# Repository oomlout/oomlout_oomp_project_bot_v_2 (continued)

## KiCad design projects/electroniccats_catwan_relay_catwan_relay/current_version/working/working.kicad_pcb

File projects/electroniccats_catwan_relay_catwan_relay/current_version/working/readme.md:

# catwan_relay
 
## summary 
* id: electroniccats_catwan_relay_catwan_relay
* user: electroniccats
* name: catwan_relay
* board: catwan_relay
* repo: https://github.com/ElectronicCats/CatWAN_Relay
* src_file_repo_kicad_pcb: Hw/CatWAN-Relay.kicad_pcb
* src_file_repo_kicad_pcb_link: https://github.com/ElectronicCats/CatWAN_Relay/tree/master/Hw/CatWAN-Relay.kicad_pcb
* src_file_repo_kicad_sch: Hw/CatWAN-Relay.kicad_sch
* src_file_repo_kicad_sch_link: https://github.com/ElectronicCats/CatWAN_Relay/tree/master/Hw/CatWAN-Relay.kicad_sch

* src_file_repo_sch: Hw/CatWAN-Relay.sch
* src_file_repo_sch_link: https://github.com/ElectronicCats/CatWAN_Relay/tree/master/Hw/CatWAN-Relay.sch
* full details link: https://github.com/oomlout/oomlout_oomp_project_bot_v_2/tree/main/projects/electroniccats_catwan_relay_catwan_relay/current_version/working

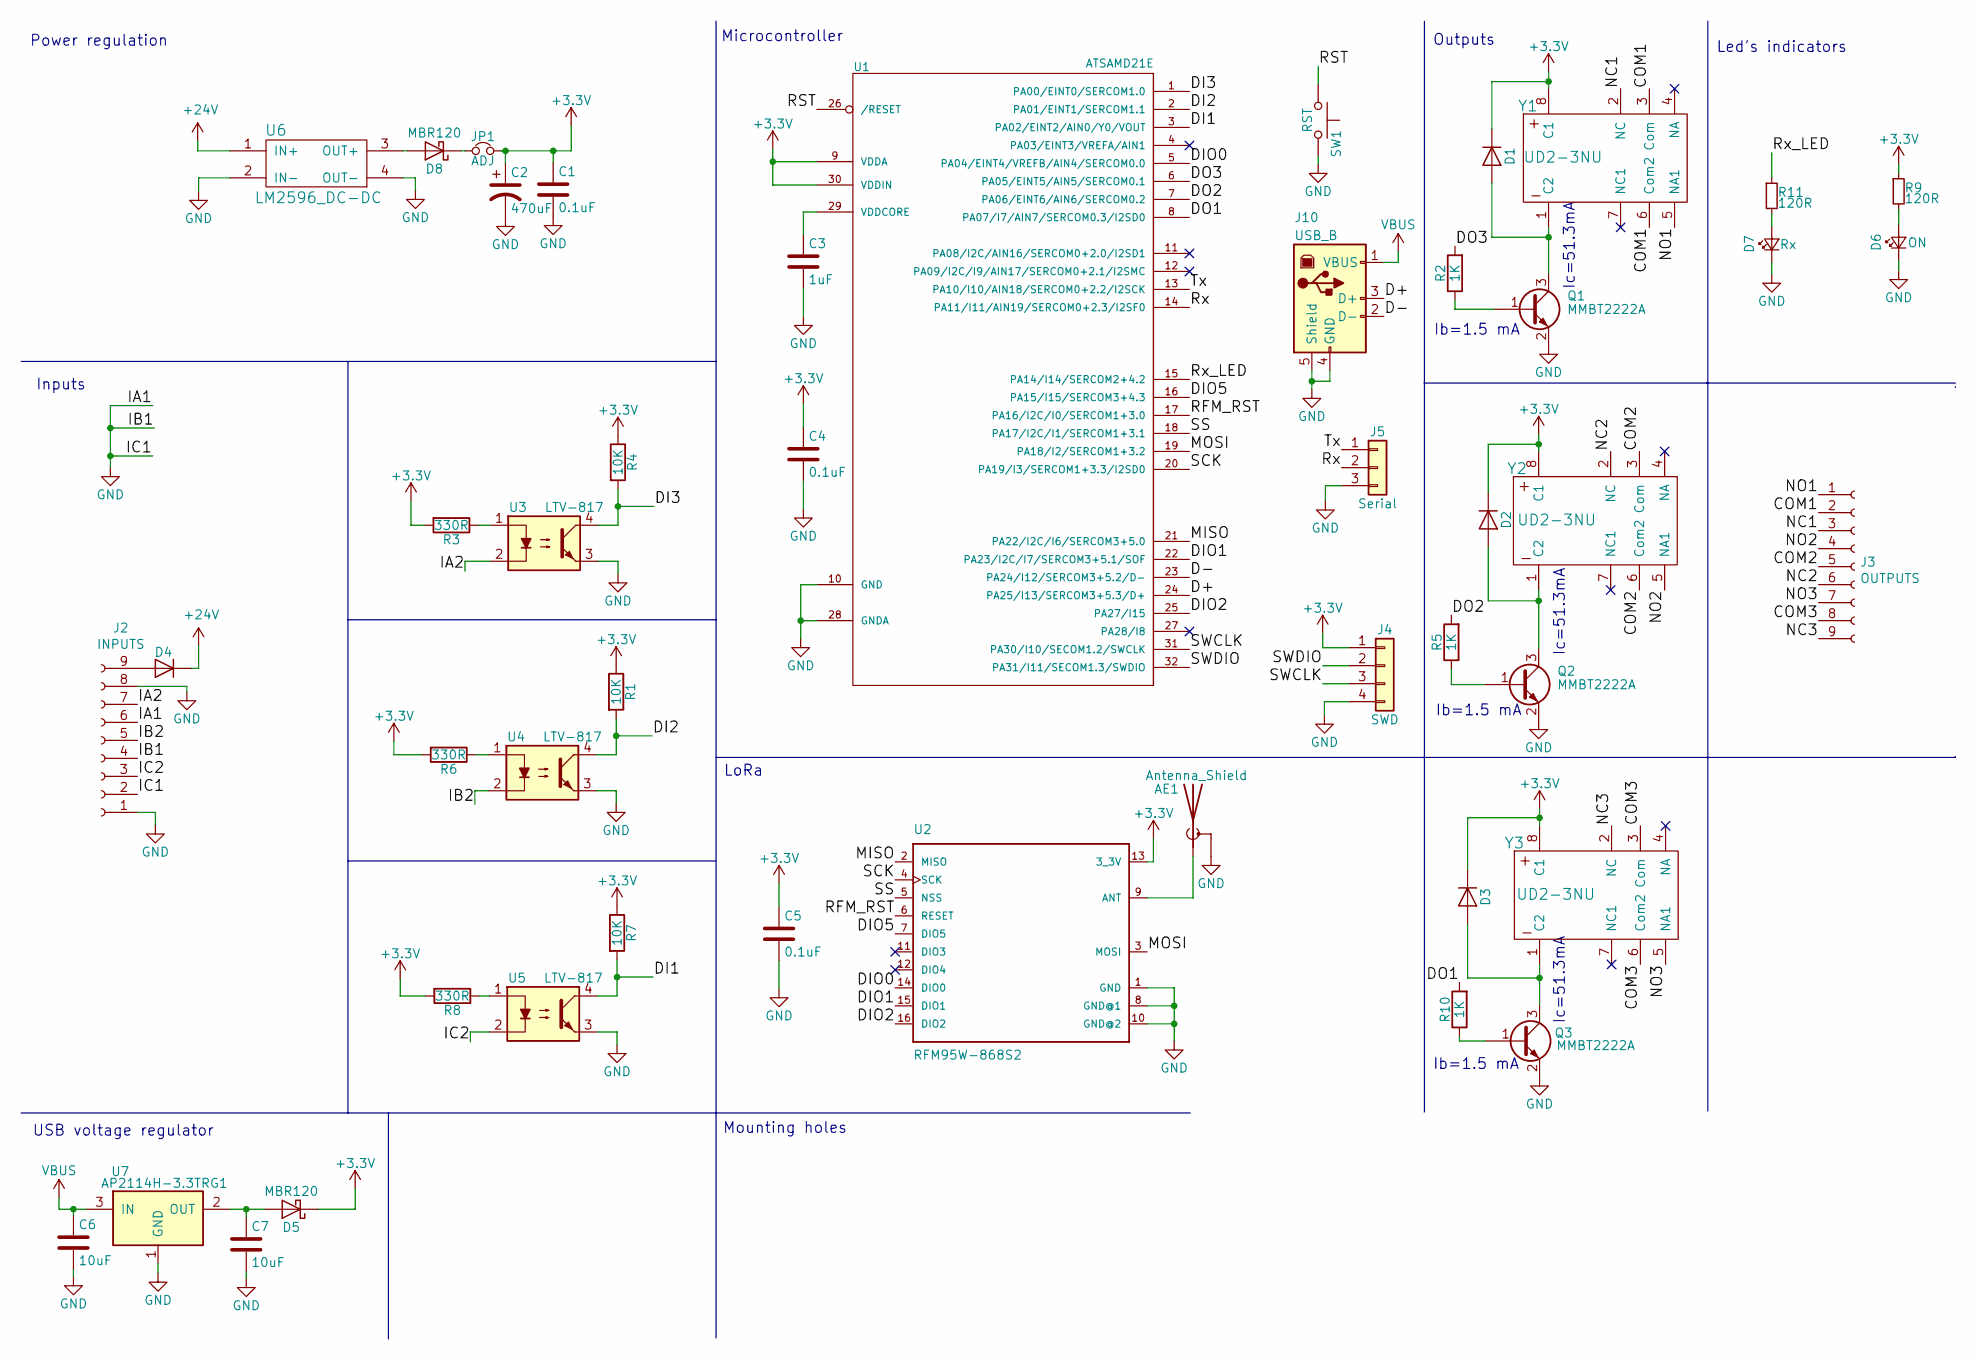
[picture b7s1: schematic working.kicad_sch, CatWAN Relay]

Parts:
AE1: Antenna_Shield; MOLEX_1661
C1, C4, C5: 0.1uF; C_0805_2012Metric_Pad1.15x1.40mm_HandSolder
C2: 470uF; C_Elec_6.3x7.7
C3: 1uF; C_0805_2012Metric_Pad1.15x1.40mm_HandSolder
C6, C7: 10uF; C_0805_2012Metric_Pad1.15x1.40mm_HandSolder
D1, D2, D3: FM4007W-W; F4007
D4: FM4007W-W; D_SOD-123
D5, D8: MBR120; D_SOD-123
D6: ON; LED_0805_2012Metric_Pad1.15x1.40mm_HandSolder
D7: Rx; LED_0805_2012Metric_Pad1.15x1.40mm_HandSolder
J2: INPUTS; TerminalBlock_Phoenix_MKDS-1,5-9-5.08_1x09_P5.08mm_Horizont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
J3: OUTPUTS; TerminalBlock_Phoenix_MKDS-1,5-9-5.08_1x09_P5.08mm_Horizont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
J4: SWD; PinHeader_1x04_P2.54mm_Vertical
J5: Serial; PinHeader_1x03_P2.54mm_Vertical
J10: USB_B; 629105150521
JP1: ADJ; PinHeader_1x02_P2.54mm_Vertical
Q1, Q2, Q3: MMBT2222A; SOT-23
R1, R4, R7: 10K; R_0805_2012Metric_Pad1.15x1.40mm_HandSolder
R2, R5, R10: 1K; R_0805_2012Metric_Pad1.15x1.40mm_HandSolder
R3, R6, R8: 330R; R_0805_2012Metric_Pad1.15x1.40mm_HandSolder
R9, R11: 120R; R_0805_2012Metric_Pad1.15x1.40mm_HandSolder
SW1: RST; SW_SPST_TL3342
U1: ATSAMD21E; TQFP-32_7x7mm_P0.8mm
U2: RFM95W-868S2; RFM95W
U3, U4, U5: LTV-817; DIP-4_W7.62mm_Socket
U6: LM2596_DC-DC; LM2596DC-DC
U7: AP2114H-3.3TRG1; SOT-223-3_TabPin2
Y1, Y2, Y3: UD2-3NU

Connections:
+3V3: C1.1, C2.1, C4.1, C5.1, D1.1 (K), D2.1 (K), D3.1 (K), D5.1 (K), J4.1, JP1.2, R1.1, R3.2, R4.1, R6.2, R7.1, R8.2, R9.1, U1.9 (VDDA), U1.30 (VDDIN), U2.13 (3_3V), Y1.8 (C1), Y2.8 (C1), Y3.8 (C1)
+24V: D4.1 (K), U6.1 (IN+)
/COM1: J3.2, Y1.3 (Com), Y1.6 (Com2)
/COM2: J3.5, Y2.3 (Com), Y2.6 (Com2)
/COM3: J3.8, Y3.3 (Com), Y3.6 (Com2)
/D+: J10.3 (D+), U1.24 (PA25/I13/SERCOM3+5.3/D+)
/D-: J10.2 (D-), U1.23 (PA24/I12/SERCOM3+5.2/D-)
/DI1: R7.2, U1.3 (PA02/EINT2/AIN0/Y0/VOUT), U5.4
/DI2: R1.2, U1.2 (PA01/EINT1/SERCOM1.1), U4.4
/DI3: R4.2, U1.1 (PA00/EINT0/SERCOM1.0), U3.4
/DIO0: U1.5 (PA04/EINT4/VREFB/AIN4/SERCOM0.0), U2.14 (DIO0)
/DIO1: U1.22 (PA23/I2C/I7/SERCOM3+5.1/SOF), U2.15 (DIO1)
/DIO2: U1.25 (PA27/I15), U2.16 (DIO2)
/DIO5: U1.16 (PA15/I15/SERCOM3+4.3), U2.7 (DIO5)
/DO1: R10.2, U1.8 (PA07/I7/AIN7/SERCOM0.3/I2SD0)
/DO2: R5.2, U1.7 (PA06/EINT6/AIN6/SERCOM0.2)
/DO3: R2.2, U1.6 (PA05/EINT5/AIN5/SERCOM0.1)
/IA2: J2.7, U3.2
/IB2: J2.5, U4.2
/IC2: J2.3, U5.2
/MISO: U1.21 (PA22/I2C/I6/SERCOM3+5.0), U2.2 (MISO)
/MOSI: U1.19 (PA18/I2/SERCOM1+3.2), U2.3 (MOSI)
/NC1: J3.3, Y1.2 (NC)
/NC2: J3.6, Y2.2 (NC)
/NC3: J3.9, Y3.2 (NC)
/NO1: J3.1, Y1.5 (NA1)
/NO2: J3.4, Y2.5 (NA1)
/NO3: J3.7, Y3.5 (NA1)
/RFM_RST: U1.17 (PA16/I2C/I0/SERCOM1+3.0), U2.6 (RESET)
/RST: SW1.1, U1.26 (/RESET)
/Rx: J5.2, U1.14 (PA11/I11/AIN19/SERCOM0+2.3/I2SF0)
/Rx_LED: R11.1, U1.15 (PA14/I14/SERCOM2+4.2)
/SCK: U1.20 (PA19/I3/SERCOM1+3.3/I2SD0), U2.4 (SCK)
/SS: U1.18 (PA17/I2C/I1/SERCOM1+3.1), U2.5 (NSS)
/SWCLK: J4.3, U1.31 (PA30/I10/SECOM1.2/SWCLK)
/SWDIO: J4.2, U1.32 (PA31/I11/SECOM1.3/SWDIO)
/Tx: J5.1, U1.13 (PA10/I10/AIN18/SERCOM0+2.2/I2SCK)
GND: AE1.2 (Shield), C1.2, C2.2, C3.2, C4.2, C5.2, C6.2, C7.2, D6.1 (K), D7.1 (K), J2.1, J2.2, J2.4, J2.6, J2.8, J4.4, J5.3, J10.4 (GND), J10.5 (Shield), Q1.2 (E), Q2.2 (E), Q3.2 (E), SW1.2, U1.10 (GND), U1.28 (GNDA), U2.1 (GND), U2.8 (GND@1), U2.10 (GND@2), U3.3, U4.3, U5.3, U6.2 (IN-), U6.4 (OUT-), U7.1 (GND)
unnamed: AE1.1 (A), U2.9 (ANT)
unnamed: C3.1, U1.29 (VDDCORE)
unnamed: C7.1, D5.2 (A), U7.2 (OUT)
unnamed: D1.2 (A), Q1.3 (C), Y1.1 (C2)
unnamed: D2.2 (A), Q2.3 (C), Y2.1 (C2)
unnamed: D3.2 (A), Q3.3 (C), Y3.1 (C2)
unnamed: D4.2 (A), J2.9
unnamed: D6.2 (A), R9.2
unnamed: D7.2 (A), R11.2
unnamed: D8.1 (K), JP1.1
unnamed: D8.2 (A), U6.3 (OUT+)
unnamed: Q1.1 (B), R2.1
unnamed: Q2.1 (B), R5.1
unnamed: Q3.1 (B), R10.1
unnamed: R3.1, U3.1
unnamed: R6.1, U4.1
unnamed: R8.1, U5.1
VBUS: C6.1, J10.1 (VBUS), U7.3 (IN)

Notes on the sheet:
Ic=51.3mA
Power regulation
Inputs
Ib=1.5 mA
LoRa
Led's indicators
Outputs
Mounting holes
Microcontroller
USB voltage regulator

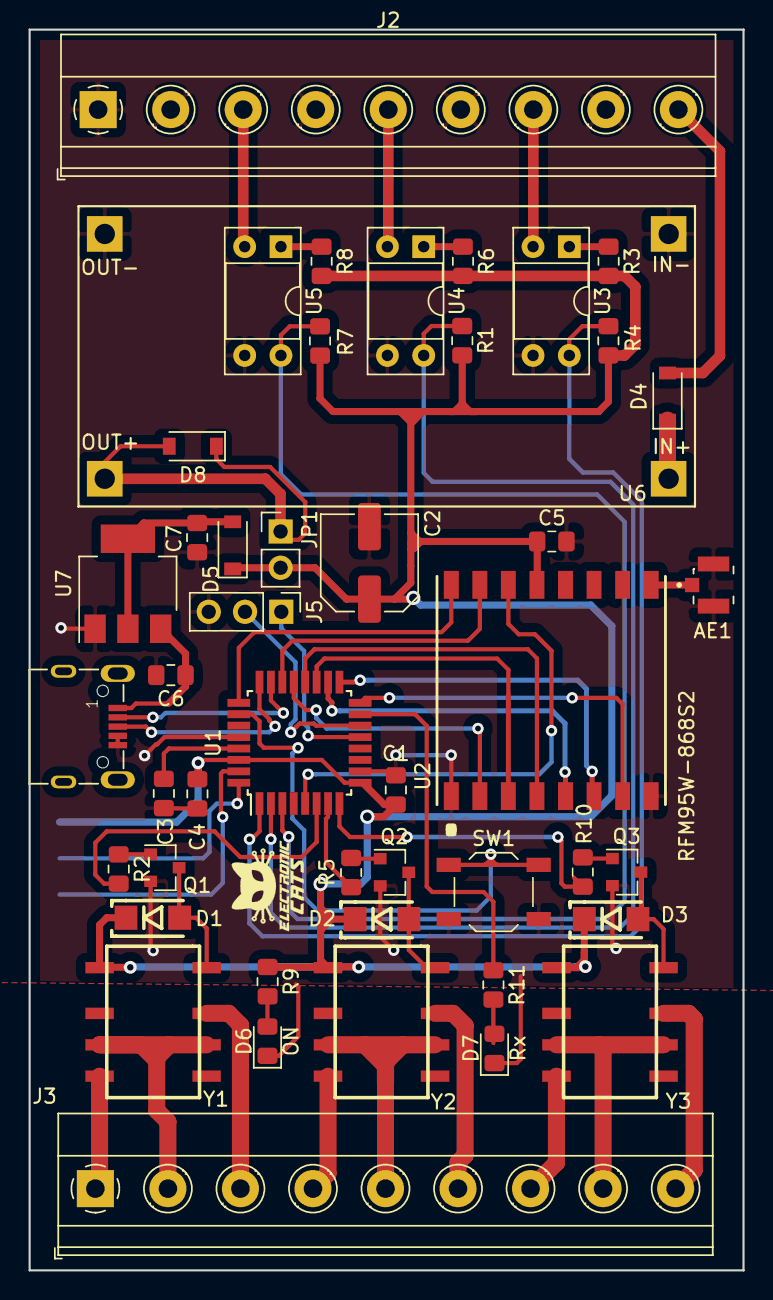
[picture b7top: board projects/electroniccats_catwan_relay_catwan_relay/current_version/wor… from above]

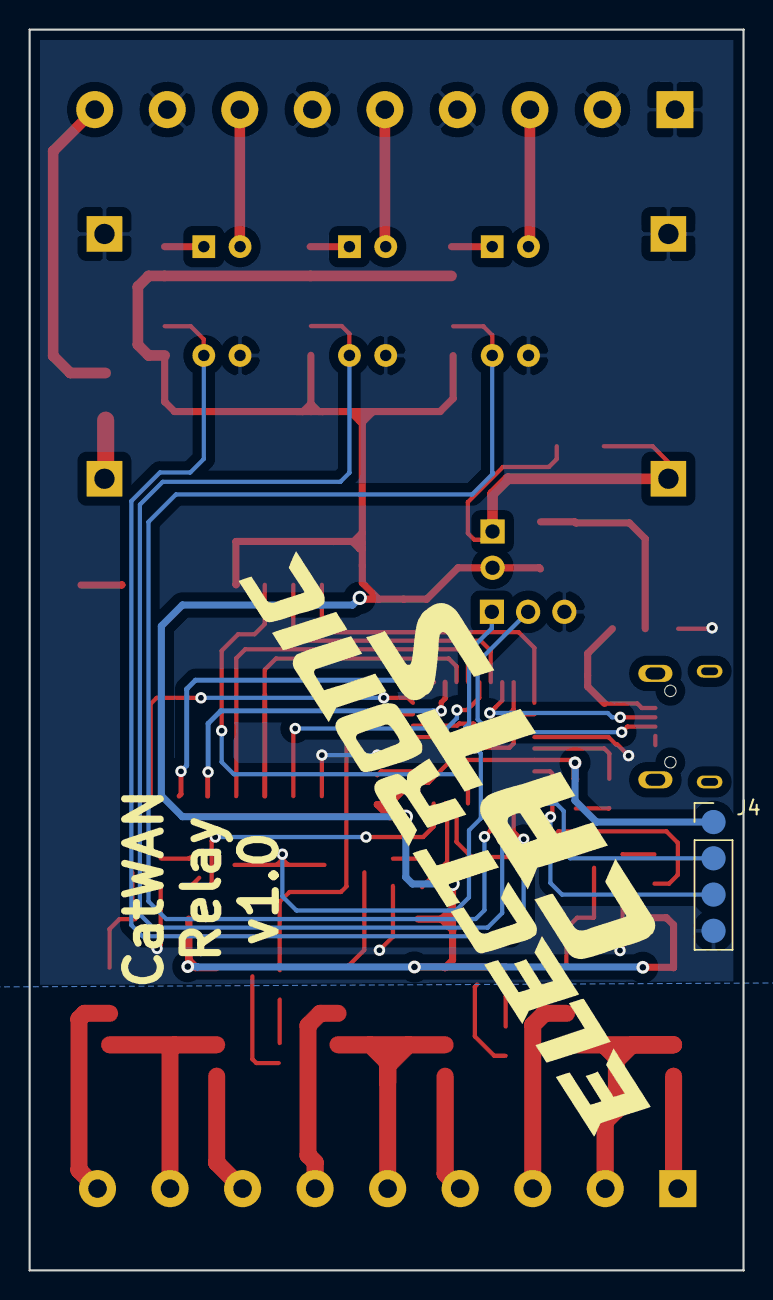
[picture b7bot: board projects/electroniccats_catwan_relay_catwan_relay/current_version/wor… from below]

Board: 2 copper layers, 50.0 x 86.9 mm, 48 parts (2 on the bottom side), 56 nets.

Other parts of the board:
svg2mod: electronic; titule_electronic_med

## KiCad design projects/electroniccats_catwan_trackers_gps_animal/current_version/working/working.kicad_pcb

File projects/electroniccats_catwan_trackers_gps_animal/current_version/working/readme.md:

# catwan_trackers
 
## summary 
* id: electroniccats_catwan_trackers_gps_animal
* user: electroniccats
* name: catwan_trackers
* board: gps_animal
* repo: https://github.com/ElectronicCats/CatWAN_Trackers
* src_file_repo_kicad_pcb: Hardware/gps_animal/gps_animal.kicad_pcb
* src_file_repo_kicad_pcb_link: https://github.com/ElectronicCats/CatWAN_Trackers/tree/master/Hardware/gps_animal/gps_animal.kicad_pcb

* src_file_repo_sch: Hardware/gps_animal/gps_animal.sch
* src_file_repo_sch_link: https://github.com/ElectronicCats/CatWAN_Trackers/tree/master/Hardware/gps_animal/gps_animal.sch
* full details link: https://github.com/oomlout/oomlout_oomp_project_bot_v_2/tree/main/projects/electroniccats_catwan_trackers_gps_animal/current_version/working

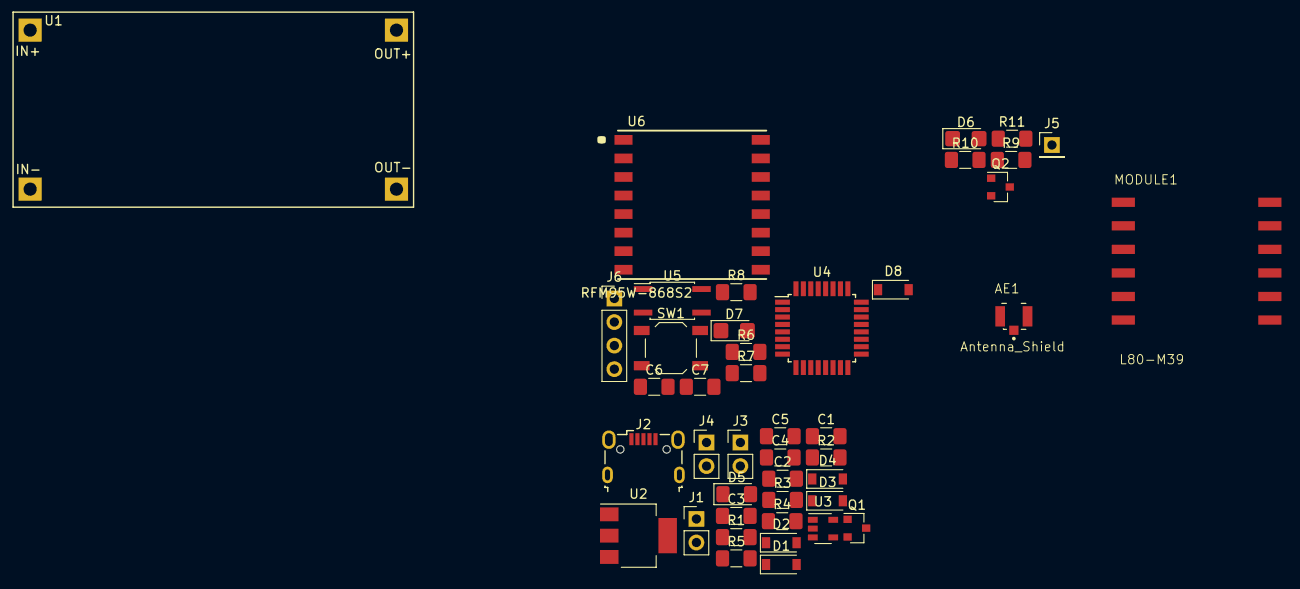
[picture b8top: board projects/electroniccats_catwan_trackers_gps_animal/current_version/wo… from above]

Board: 2 copper layers, 43 parts (0 on the bottom side), 40 nets, no tracks yet.

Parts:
AE1: Antenna_Shield; MOLEX_1661
C1, C2, C5: 10uf; C_1206_3216Metric_Pad1.42x1.75mm_HandSolder
C3: 100uf; C_1206_3216Metric_Pad1.42x1.75mm_HandSolder
C4, C7: 0.1uf; C_1206_3216Metric_Pad1.42x1.75mm_HandSolder
C6: 1uf; C_1206_3216Metric_Pad1.42x1.75mm_HandSolder
D1, D2, D3, D4, D8: D_Schottky; D_SOD-123
D5: LED; LED_1206_3216Metric_Pad1.42x1.75mm_HandSolder
D6: LED_GREEN; LED_1206_3216Metric_Castellated
D7: LED_RED; LED_1206_3216Metric_Castellated
J1: IN 12V; PinHeader_1x02_P2.54mm_Vertical
J2: USB_B; USB_Micro-B_Wuerth_629105150521
J3: ADJ; PinHeader_1x02_P2.54mm_Vertical
J4: BAT; PinHeader_1x02_P2.54mm_Vertical
J5: PANI; PinHeader_1x01_P2.54mm_Vertical
J6: SWD; PinHeader_1x04_P2.54mm_Vertical
MODULE1: L80-M39; QUECTEL_L80-M39
Q1: Q_PMOS_GSD; SOT-23
Q2: SMMBT3904LT1G; SOT-23
R1: 47k; R_1206_3216Metric_Pad1.42x1.75mm_HandSolder
R2: 2k; R_1206_3216Metric_Pad1.42x1.75mm_HandSolder
R3, R6, R8, R10: 330; R_1206_3216Metric_Pad1.42x1.75mm_HandSolder
R4, R5: 100k; R_1206_3216Metric_Pad1.42x1.75mm_HandSolder
R7: 1k; R_1206_3216Metric_Pad1.42x1.75mm_HandSolder
R9, R11: 10k; R_1206_3216Metric_Pad1.42x1.75mm_HandSolder
SW1: RST; SW_SPST_TL3342
U1: LM2596; LM2596DC-DC
U2: AP2114-3.3; SOT-223-3_TabPin2
U3: MCP73831-3-OT; SOT-23-5
U4: ATSAMD21E; TQFP-32_7x7mm_P0.8mm
U5: LTV-352T; SO-4_4.4x3.6mm_P2.54mm
U6: RFM95W-868S2; RFM95W

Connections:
+3V3: C3.1, C4.1, C7.1, J6.4, MODULE1.4, MODULE1.5, R9.2, R10.2, R11.2, U2.2, U4.9, U4.30, U6.13
+5V: C2.1, D3.1, D4.2, D5.2, J3.2, Q1.1, R1.1, U3.4
+12V: D1.1, R7.2, U1.1
+BATT: C5.1, J4.2, Q1.2, R4.1, U3.3
/microcontroller/DIO0: U4.5, U6.14
/microcontroller/DIO1: U4.22, U6.15
/microcontroller/DIO2: U4.25, U6.16
/microcontroller/DIO5: U4.16, U6.7
/microcontroller/MISO: U4.21, U6.2
/microcontroller/MOSI: U4.19, U6.3
/microcontroller/NSS: U4.18, U6.5
/microcontroller/RST_RF: U4.17, U6.6
/microcontroller/RST_SAMD: SW1.2, U4.26
/microcontroller/RX_GPS: MODULE1.1, U4.14
/microcontroller/SCK: U4.20, U6.4
/microcontroller/SIG_CONECTADO: Q2.3, R9.1
/microcontroller/SIG_PANI: R11.1, U5.4
/microcontroller/SWCLK: J6.2, U4.31
/microcontroller/SWDIO: J6.3, U4.32
/microcontroller/TX_GPS: MODULE1.2, U4.13
/microcontroller/VDD_CORE: C6.1, U4.29
D+: J2.3, U4.24
D-: J2.2, U4.23
GND: AE1.2, C1.2, C2.2, C3.2, C4.2, C5.2, C6.2, C7.2, J1.2, J2.4, J2.5, J4.1, J6.1, MODULE1.3, MODULE1.12, Q2.2, R1.2, R2.2, R5.2, R6.2, R8.2, SW1.1, U1.2, U1.4, U2.1, U3.2, U4.10, U4.28, U5.3, U6.1, U6.8, U6.10
unnamed: AE1.1, U6.9
unnamed: C1.1, D4.1, Q1.3, U2.3
unnamed: D1.2, J1.1
unnamed: D2.1, J3.1
unnamed: D2.2, U1.3
unnamed: D3.2, J2.1
unnamed: D5.1, R3.1
unnamed: D6.1, R6.1
unnamed: D7.1, R8.1
unnamed: D8.1, J5.1
unnamed: D8.2, U5.2
unnamed: Q2.1, R7.1
unnamed: R2.1, U3.5
unnamed: R3.2, U3.1
unnamed: R10.1, U5.1
V_DIV: R4.2, R5.1
